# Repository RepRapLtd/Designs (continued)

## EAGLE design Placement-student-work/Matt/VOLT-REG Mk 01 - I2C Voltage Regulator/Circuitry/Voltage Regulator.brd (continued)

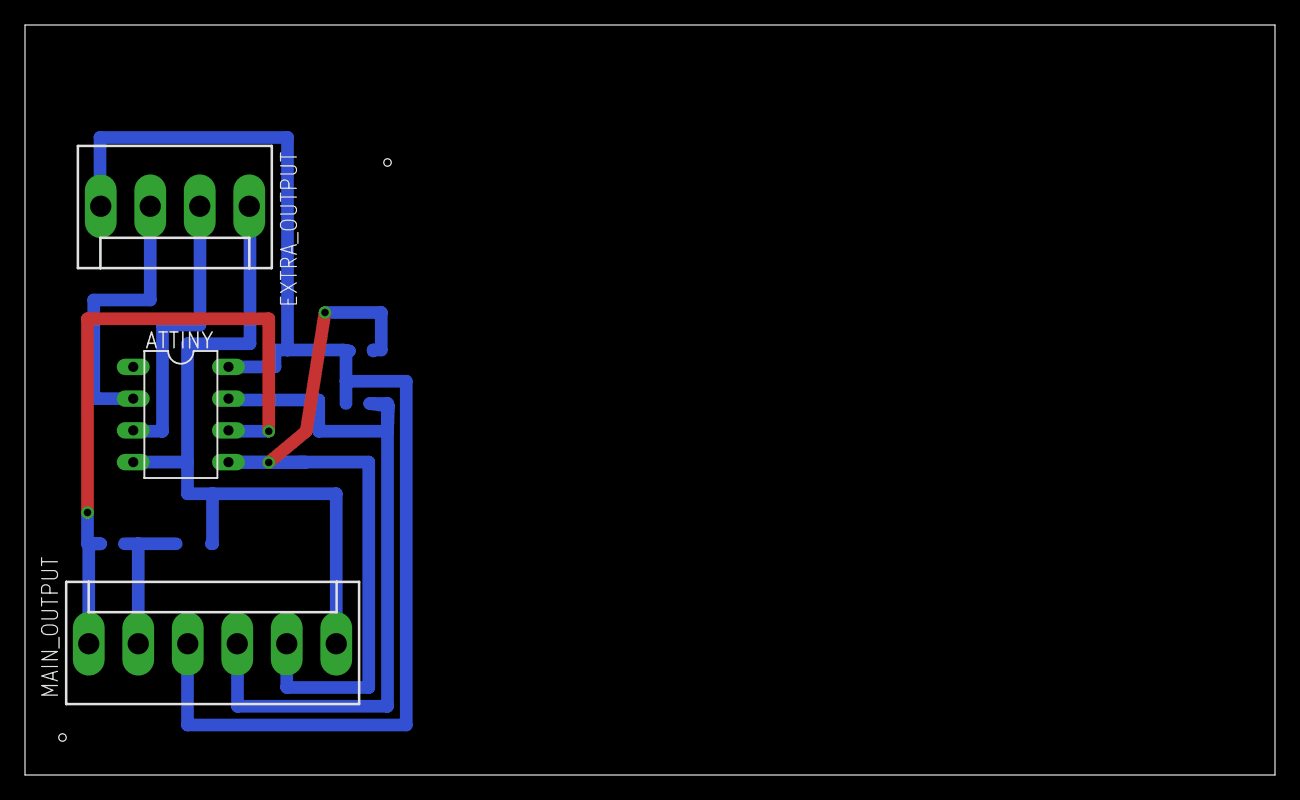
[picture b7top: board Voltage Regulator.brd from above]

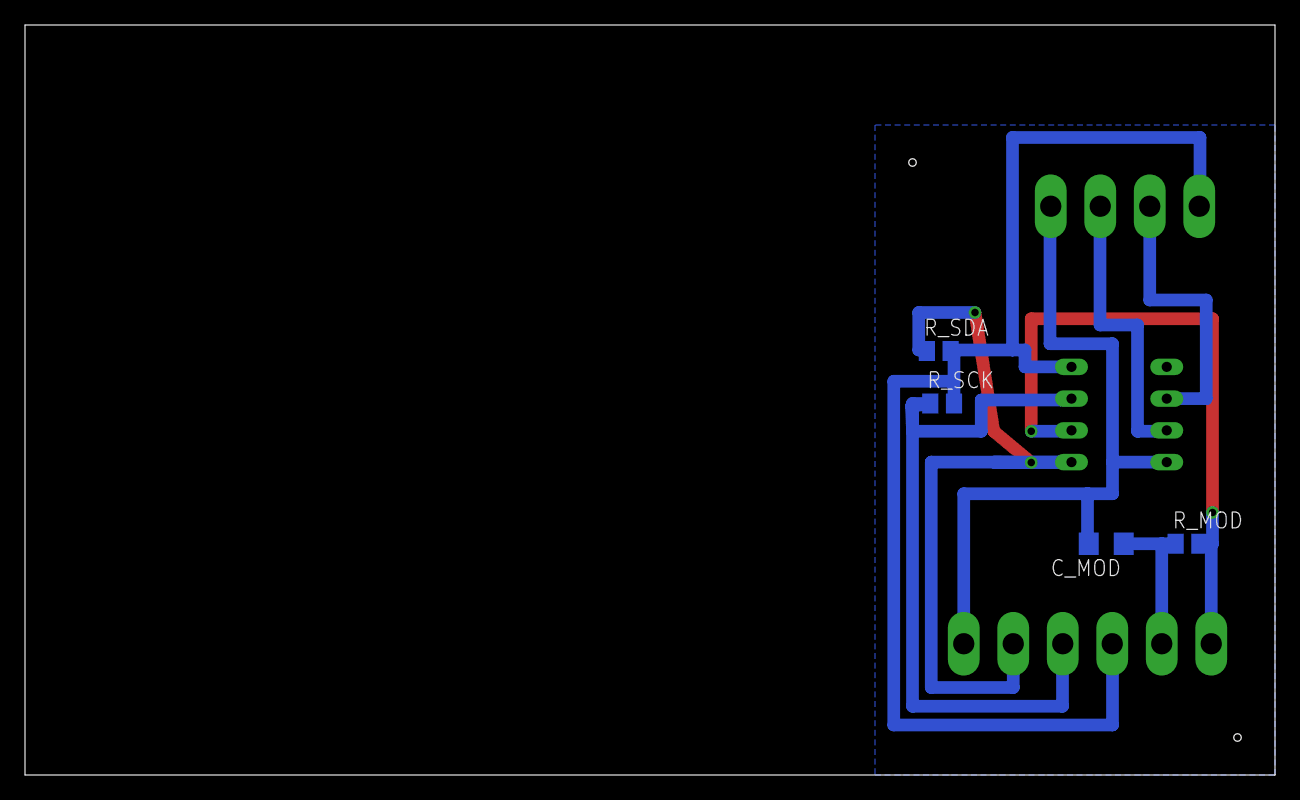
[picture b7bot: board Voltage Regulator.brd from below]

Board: 2 copper layers, 100.0 x 60.0 mm, 7 parts (4 on the bottom side), 8 nets.

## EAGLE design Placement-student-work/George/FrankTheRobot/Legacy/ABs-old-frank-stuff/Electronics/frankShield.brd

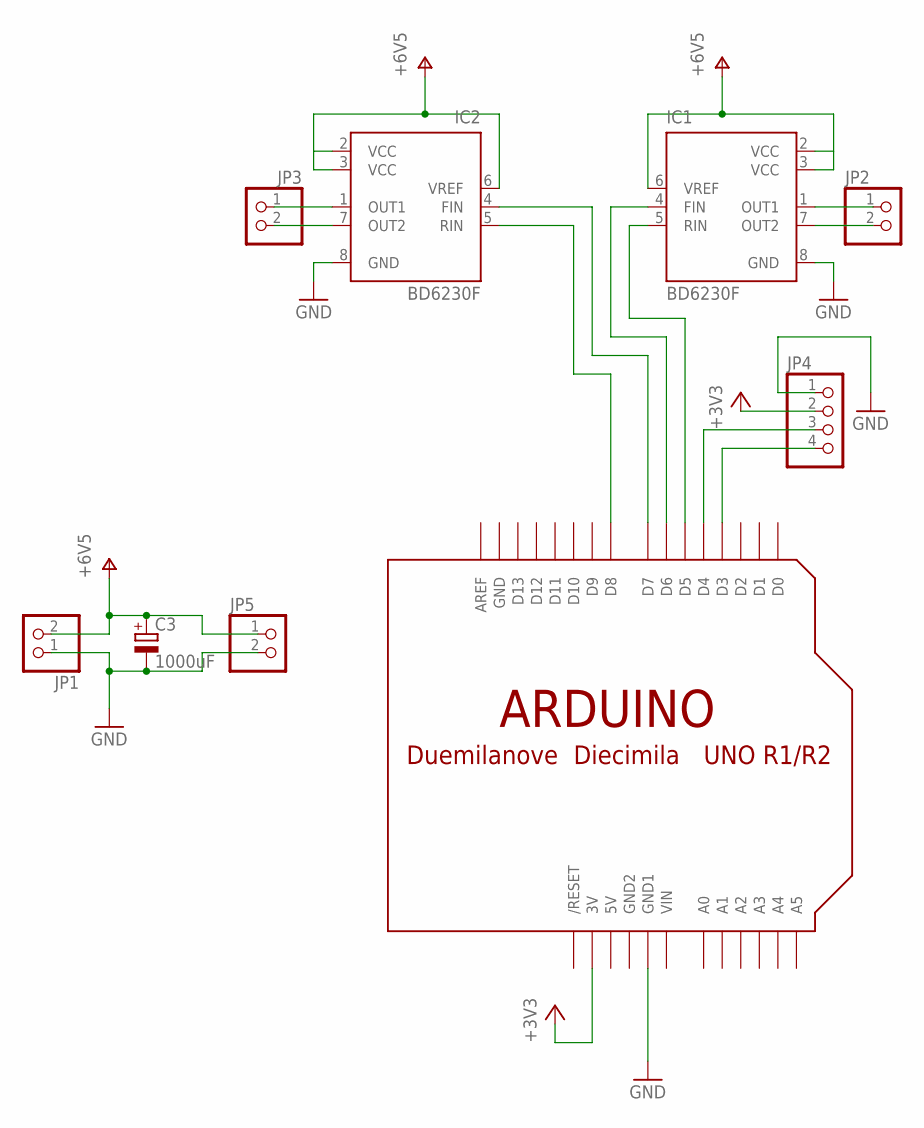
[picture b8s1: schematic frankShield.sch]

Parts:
C3: 1000uF; B45181B
IC1, IC2: BD6230F; SOP8
JP1, JP2, JP3, JP5: PINHD-1X2; 1X02
JP4: PINHD-1X4; 1X04
U$1: ARDUINO-BPLACE

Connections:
5V: U$1.5V
+3V3: JP4.2, U$1.3V
GND: C3.-, IC1.8 (GND), IC2.8 (GND), JP1.1, JP4.1, JP5.2, U$1.GND, U$1.GND1
GND2: U$1.GND2
unnamed: JP4.4, U$1.D3
unnamed: JP4.3, U$1.D4
unnamed: IC1.1 (OUT1), JP2.1
unnamed: IC1.7 (OUT2), JP2.2
unnamed: IC2.1 (OUT1), JP3.1
unnamed: IC2.7 (OUT2), JP3.2
unnamed: IC1.5 (RIN), U$1.D5
unnamed: IC1.4 (FIN), U$1.D6
unnamed: IC2.4 (FIN), U$1.D7
unnamed: IC2.5 (RIN), U$1.D8
V+: C3.+, IC1.2 (VCC), IC1.3 (VCC), IC1.6 (VREF), IC2.2 (VCC), IC2.3 (VCC), IC2.6 (VREF), JP1.2, JP5.1
VIN: U$1.VIN

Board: 2 copper layers, 9 parts (0 on the bottom side), 13 nets, no tracks yet.

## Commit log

2019-09-13 Sorting out move from old defunct account.
2024-05-29 Updating designs
2024-05-29 Updating...
2024-08-09 Added the Python air-vent macro.
2024-08-09 RM for vent
2024-08-09 spelling
2024-08-09 Now with PDF...
2024-10-07 Added air vent image etc.
